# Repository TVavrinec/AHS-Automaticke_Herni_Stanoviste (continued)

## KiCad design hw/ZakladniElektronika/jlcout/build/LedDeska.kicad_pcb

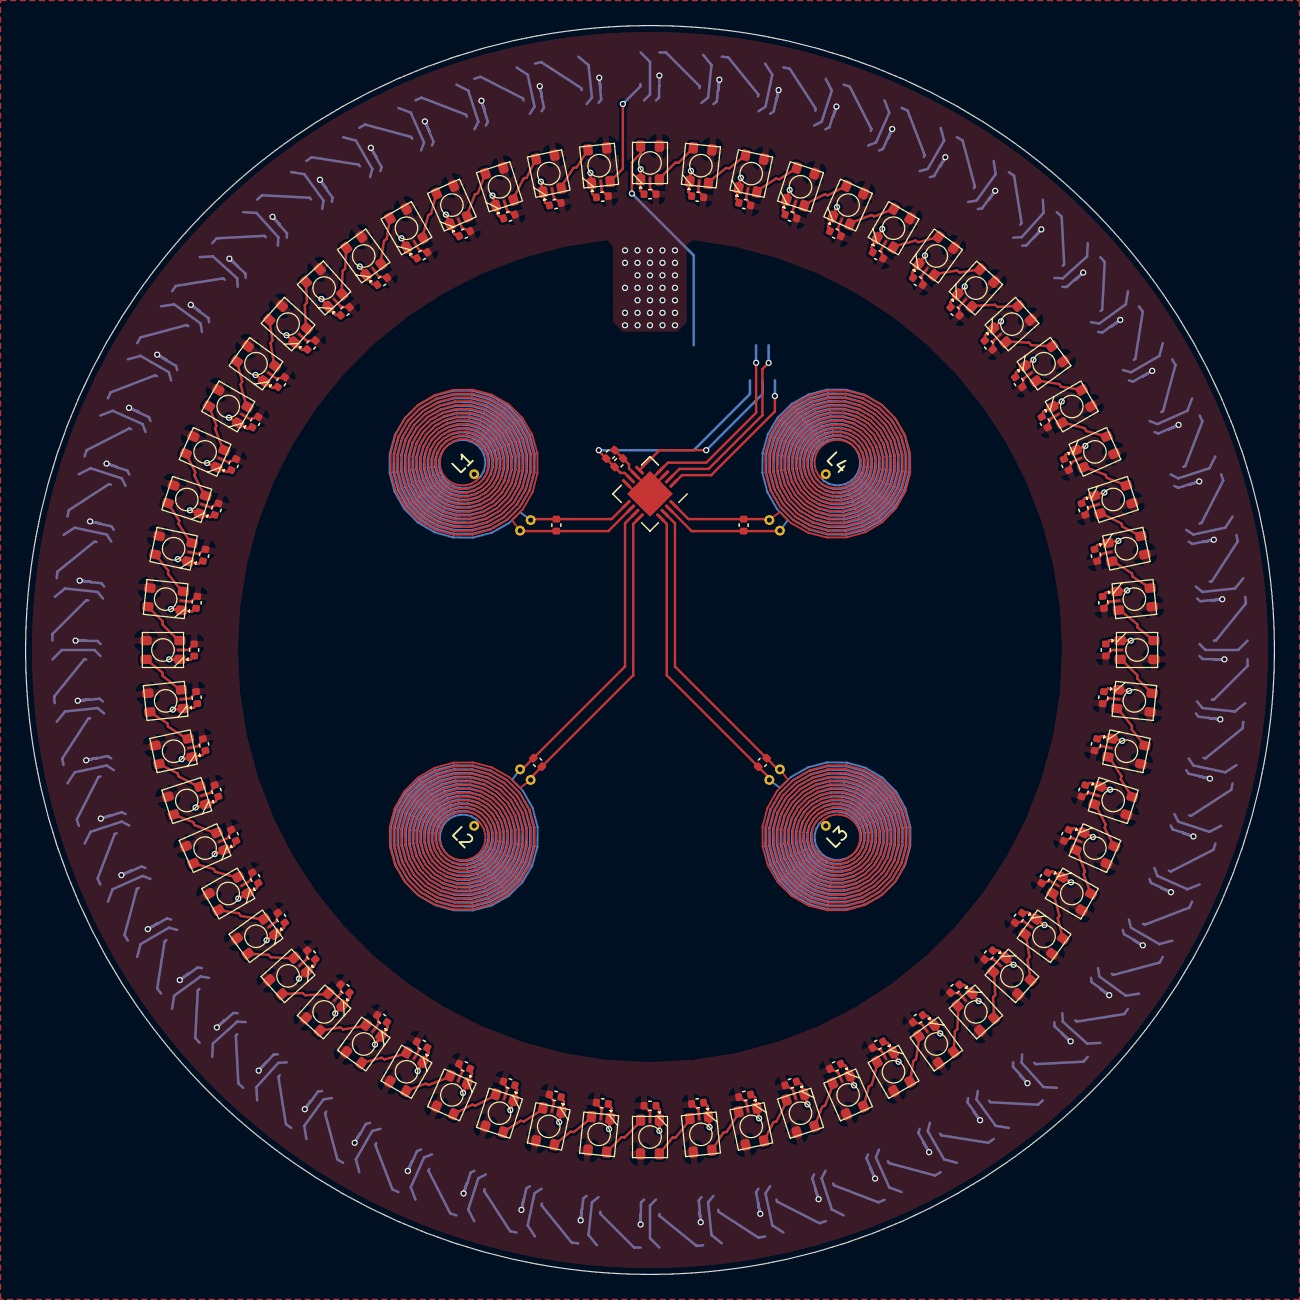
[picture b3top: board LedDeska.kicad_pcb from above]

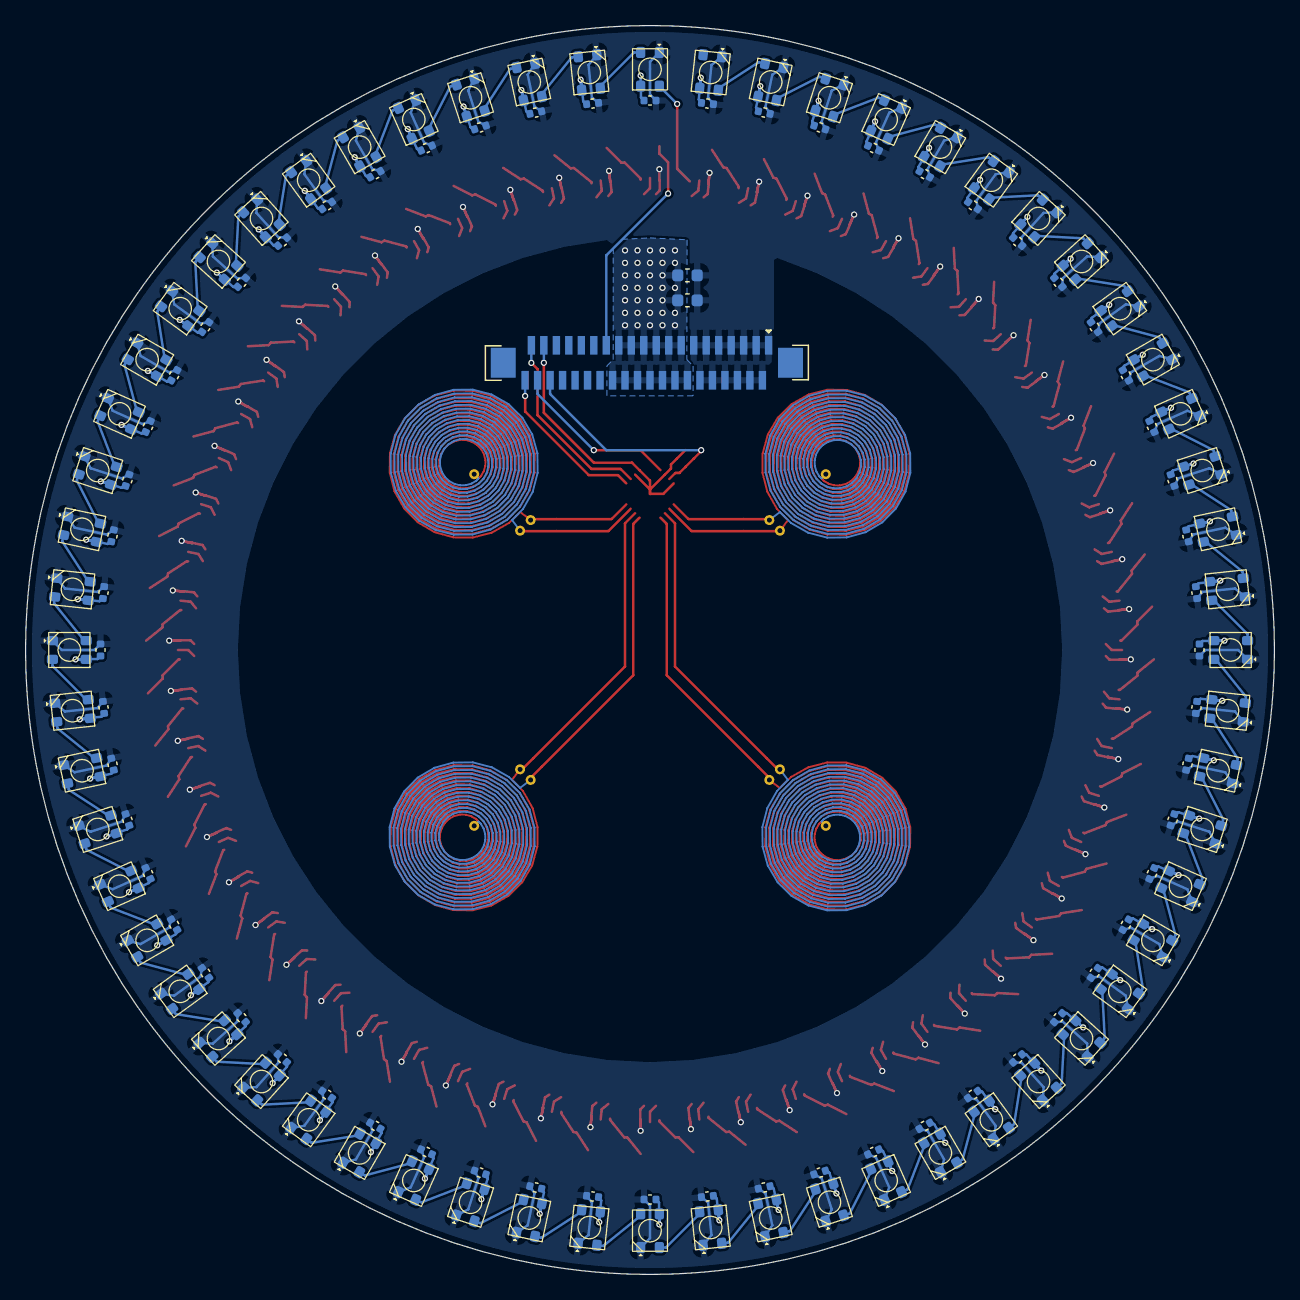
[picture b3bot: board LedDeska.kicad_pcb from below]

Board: 2 copper layers, 100.0 x 100.0 mm, 254 parts (123 on the bottom side), 135 nets.

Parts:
C1, C2: 10u; C_0603_1608Metric
C3: 1u; C_0402_1005Metric
C4, C12, C13, C14, C15, C16, C17, C18, C19, C20, C21, C22, C23, C24, C25, C26, C27, C28, C29, C30, C31, C32, C33, C34, C35, C36, C37, C38, C39, C40, C41, C42, C43, C44, C45, C46, C47, C48, C49, C50, C51, C52, C53, C54, C55, C56, C57, C58, C59, C60, C61, C62, C63, C64, C65, C66, C67, C68, C69, C70, C71, C72, C73, C74, C75, C76, C77, C78, C79, C80, C81, C82, C83, C84, C85, C86, C87, C88, C89, C90, C91, C92, C93, C94, C95, C96, C97, C98, C99, C100, C101, C102, C103, C104, C105, C106, C107, C108, C109, C110, C111, C112, C113, C114, C115, C116, C117, C118, C119, C120, C121, C122, C123, C124, C125, C126, C127, C128, C129, C130, C131: 100n; C_0402_1005Metric
C8, C9, C10, C11: 1000p; C_0402_1005Metric
D1, D2, D3, D4, D5, D6, D7, D8, D9, D10, D11, D12, D13, D14, D15, D16, D17, D18, D19, D20, D21, D22, D23, D24, D25, D26, D27, D28, D29, D30, D31, D32, D33, D34, D35, D36, D37, D38, D39, D40, D41, D42, D43, D44, D45, D46, D47, D48, D49, D50, D51, D52, D53, D54, D55, D56, D57, D58, D59, D60, D61, D62, D63, D64, D65, D66, D67, D68, D69, D70, D71, D72, D73, D74, D75, D76, D77, D78, D79, D80, D81, D82, D83, D84, D85, D86, D87, D88, D89, D90, D91, D92, D93, D94, D95, D96, D97, D98, D99, D100, D101, D102, D103, D104, D105, D106, D107, D108, D109, D110, D111, D112, D113, D114, D115, D116, D117, D118, D119, D120: WS2812B; 3528RGBW-WS2812B
J10: Conn_01x40; AFC11-S40ICC-00
L1, L2, L3, L4: 5.738 µH; PCB_coil
U1: LDC1614; WQFN-16-1EP_4x4mm_P0.5mm_EP2.6x2.6mm

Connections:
/LedDeska/3V3: C3.1, C4.1, J10.36, U1.7 (VDD)
/LedDeska/5V: C1.1, C2.1, C12.1, C13.1, C14.1, C15.1, C16.1, C17.1, C18.1, C19.1, C20.1, C21.1, C22.1, C23.1, C24.1, C25.1, C26.1, C27.1, C28.1, C29.1, C30.1, C31.1, C32.1, C33.1, C34.1, C35.1, C36.1, C37.1, C38.1, C39.1, C40.1, C41.1, C42.1, C43.1, C44.1, C45.1, C46.1, C47.1, C48.1, C49.1, C50.1, C51.1, C52.1, C53.1, C54.1, C55.1, C56.1, C57.1, C58.1, C59.1, C60.1, C61.1, C62.1, C63.1, C64.1, C65.1, C66.1, C67.1, C68.1, C69.1, C70.1, C71.1, C72.1, C73.1, C74.1, C75.1, C76.1, C77.1, C78.1, C79.1, C80.1, C81.1, C82.1, C83.1, C84.1, C85.1, C86.1, C87.1, C88.1, C89.1, C90.1, C91.1, C92.1, C93.1, C94.1, C95.1, C96.1, C97.1, C98.1, C99.1, C100.1, C101.1, C102.1, C103.1, C104.1, C105.1, C106.1, C107.1, C108.1, C109.1, C110.1, C111.1, C112.1, C113.1, C114.1, C115.1, C116.1, C117.1, C118.1, C119.1, C120.1, C121.1, C122.1, C123.1, C124.1, C125.1, C126.1, C127.1, C128.1, C129.1, C130.1, C131.1, D1.1 (VDD), D2.1 (VDD), D3.1 (VDD), D4.1 (VDD), D5.1 (VDD), D6.1 (VDD), D7.1 (VDD), D8.1 (VDD), D9.1 (VDD), D10.1 (VDD), D11.1 (VDD), D12.1 (VDD), D13.1 (VDD), D14.1 (VDD), D15.1 (VDD), D16.1 (VDD), D17.1 (VDD), D18.1 (VDD), D19.1 (VDD), D20.1 (VDD), D21.1 (VDD), D22.1 (VDD), D23.1 (VDD), D24.1 (VDD), D25.1 (VDD), D26.1 (VDD), D27.1 (VDD), D28.1 (VDD), D29.1 (VDD), D30.1 (VDD), D31.1 (VDD), D32.1 (VDD), D33.1 (VDD), D34.1 (VDD), D35.1 (VDD), D36.1 (VDD), D37.1 (VDD), D38.1 (VDD), D39.1 (VDD), D40.1 (VDD), D41.1 (VDD), D42.1 (VDD), D43.1 (VDD), D44.1 (VDD), D45.1 (VDD), D46.1 (VDD), D47.1 (VDD), D48.1 (VDD), D49.1 (VDD), D50.1 (VDD), D51.1 (VDD), D52.1 (VDD), D53.1 (VDD), D54.1 (VDD), D55.1 (VDD), D56.1 (VDD), D57.1 (VDD), D58.1 (VDD), D59.1 (VDD), D60.1 (VDD), D61.1 (VDD), D62.1 (VDD), D63.1 (VDD), D64.1 (VDD), D65.1 (VDD), D66.1 (VDD), D67.1 (VDD), D68.1 (VDD), D69.1 (VDD), D70.1 (VDD), D71.1 (VDD), D72.1 (VDD), D73.1 (VDD), D74.1 (VDD), D75.1 (VDD), D76.1 (VDD), D77.1 (VDD), D78.1 (VDD), D79.1 (VDD), D80.1 (VDD), D81.1 (VDD), D82.1 (VDD), D83.1 (VDD), D84.1 (VDD), D85.1 (VDD), D86.1 (VDD), D87.1 (VDD), D88.1 (VDD), D89.1 (VDD), D90.1 (VDD), D91.1 (VDD), D92.1 (VDD), D93.1 (VDD), D94.1 (VDD), D95.1 (VDD), D96.1 (VDD), D97.1 (VDD), D98.1 (VDD), D99.1 (VDD), D100.1 (VDD), D101.1 (VDD), D102.1 (VDD), D103.1 (VDD), D104.1 (VDD), D105.1 (VDD), D106.1 (VDD), D107.1 (VDD), D108.1 (VDD), D109.1 (VDD), D110.1 (VDD), D111.1 (VDD), D112.1 (VDD), D113.1 (VDD), D114.1 (VDD), D115.1 (VDD), D116.1 (VDD), D117.1 (VDD), D118.1 (VDD), D119.1 (VDD), D120.1 (VDD), J10.1, J10.2, J10.3, J10.4, J10.5, J10.6, J10.7, J10.8, J10.9, J10.10, J10.11, J10.12, J10.13
/LedDeska/AN-GND: C3.2, C4.2, J10.37, U1.3 (CLKIN), U1.4 (ADDR), U1.6 (SD), U1.8 (GND), U1.17 (GND)
/LedDeska/INT-LDC: J10.38, U1.5 (INTB)
/LedDeska/LED-GND: C1.2, C2.2, C12.2, C13.2, C14.2, C15.2, C16.2, C17.2, C18.2, C19.2, C20.2, C21.2, C22.2, C23.2, C24.2, C25.2, C26.2, C27.2, C28.2, C29.2, C30.2, C31.2, C32.2, C33.2, C34.2, C35.2, C36.2, C37.2, C38.2, C39.2, C40.2, C41.2, C42.2, C43.2, C44.2, C45.2, C46.2, C47.2, C48.2, C49.2, C50.2, C51.2, C52.2, C53.2, C54.2, C55.2, C56.2, C57.2, C58.2, C59.2, C60.2, C61.2, C62.2, C63.2, C64.2, C65.2, C66.2, C67.2, C68.2, C69.2, C70.2, C71.2, C72.2, C73.2, C74.2, C75.2, C76.2, C77.2, C78.2, C79.2, C80.2, C81.2, C82.2, C83.2, C84.2, C85.2, C86.2, C87.2, C88.2, C89.2, C90.2, C91.2, C92.2, C93.2, C94.2, C95.2, C96.2, C97.2, C98.2, C99.2, C100.2, C101.2, C102.2, C103.2, C104.2, C105.2, C106.2, C107.2, C108.2, C109.2, C110.2, C111.2, C112.2, C113.2, C114.2, C115.2, C116.2, C117.2, C118.2, C119.2, C120.2, C121.2, C122.2, C123.2, C124.2, C125.2, C126.2, C127.2, C128.2, C129.2, C130.2, C131.2, D1.3 (VSS), D2.3 (VSS), D3.3 (VSS), D4.3 (VSS), D5.3 (VSS), D6.3 (VSS), D7.3 (VSS), D8.3 (VSS), D9.3 (VSS), D10.3 (VSS), D11.3 (VSS), D12.3 (VSS), D13.3 (VSS), D14.3 (VSS), D15.3 (VSS), D16.3 (VSS), D17.3 (VSS), D18.3 (VSS), D19.3 (VSS), D20.3 (VSS), D21.3 (VSS), D22.3 (VSS), D23.3 (VSS), D24.3 (VSS), D25.3 (VSS), D26.3 (VSS), D27.3 (VSS), D28.3 (VSS), D29.3 (VSS), D30.3 (VSS), D31.3 (VSS), D32.3 (VSS), D33.3 (VSS), D34.3 (VSS), D35.3 (VSS), D36.3 (VSS), D37.3 (VSS), D38.3 (VSS), D39.3 (VSS), D40.3 (VSS), D41.3 (VSS), D42.3 (VSS), D43.3 (VSS), D44.3 (VSS), D45.3 (VSS), D46.3 (VSS), D47.3 (VSS), D48.3 (VSS), D49.3 (VSS), D50.3 (VSS), D51.3 (VSS), D52.3 (VSS), D53.3 (VSS), D54.3 (VSS), D55.3 (VSS), D56.3 (VSS), D57.3 (VSS), D58.3 (VSS), D59.3 (VSS), D60.3 (VSS), D61.3 (VSS), D62.3 (VSS), D63.3 (VSS), D64.3 (VSS), D65.3 (VSS), D66.3 (VSS), D67.3 (VSS), D68.3 (VSS), D69.3 (VSS), D70.3 (VSS), D71.3 (VSS), D72.3 (VSS), D73.3 (VSS), D74.3 (VSS), D75.3 (VSS), D76.3 (VSS), D77.3 (VSS), D78.3 (VSS), D79.3 (VSS), D80.3 (VSS), D81.3 (VSS), D82.3 (VSS), D83.3 (VSS), D84.3 (VSS), D85.3 (VSS), D86.3 (VSS), D87.3 (VSS), D88.3 (VSS), D89.3 (VSS), D90.3 (VSS), D91.3 (VSS), D92.3 (VSS), D93.3 (VSS), D94.3 (VSS), D95.3 (VSS), D96.3 (VSS), D97.3 (VSS), D98.3 (VSS), D99.3 (VSS), D100.3 (VSS), D101.3 (VSS), D102.3 (VSS), D103.3 (VSS), D104.3 (VSS), D105.3 (VSS), D106.3 (VSS), D107.3 (VSS), D108.3 (VSS), D109.3 (VSS), D110.3 (VSS), D111.3 (VSS), D112.3 (VSS), D113.3 (VSS), D114.3 (VSS), D115.3 (VSS), D116.3 (VSS), D117.3 (VSS), D118.3 (VSS), D119.3 (VSS), D120.3 (VSS), J10.14, J10.15, J10.16, J10.17, J10.18, J10.19, J10.20, J10.21, J10.22, J10.23, J10.24, J10.25, J10.26
/LedDeska/LedRing-Axial/DOUT: D60.2 (DOUT), D61.4 (DIN)
/LedDeska/SCL: J10.40, U1.1 (SCL)
/LedDeska/SDA: J10.39, U1.2 (SDA)
/LedDeska/WS2812: D1.4 (DIN), J10.27
unnamed: D1.2 (DOUT), D2.4 (DIN)
unnamed: D2.2 (DOUT), D3.4 (DIN)
unnamed: D3.2 (DOUT), D4.4 (DIN)
unnamed: D4.2 (DOUT), D5.4 (DIN)
unnamed: D5.2 (DOUT), D6.4 (DIN)
unnamed: D6.2 (DOUT), D7.4 (DIN)
unnamed: D7.2 (DOUT), D8.4 (DIN)
unnamed: D8.2 (DOUT), D9.4 (DIN)
unnamed: D9.2 (DOUT), D10.4 (DIN)
unnamed: D10.2 (DOUT), D11.4 (DIN)
unnamed: D11.2 (DOUT), D12.4 (DIN)
unnamed: D12.2 (DOUT), D13.4 (DIN)
unnamed: D13.2 (DOUT), D14.4 (DIN)
unnamed: D14.2 (DOUT), D15.4 (DIN)
unnamed: D15.2 (DOUT), D16.4 (DIN)
unnamed: D16.2 (DOUT), D17.4 (DIN)
unnamed: D17.2 (DOUT), D18.4 (DIN)
unnamed: D18.2 (DOUT), D19.4 (DIN)
unnamed: D19.2 (DOUT), D20.4 (DIN)
unnamed: D20.2 (DOUT), D21.4 (DIN)
unnamed: D21.2 (DOUT), D22.4 (DIN)
unnamed: D22.2 (DOUT), D23.4 (DIN)
unnamed: D23.2 (DOUT), D24.4 (DIN)
unnamed: D24.2 (DOUT), D25.4 (DIN)
unnamed: D25.2 (DOUT), D26.4 (DIN)
unnamed: D26.2 (DOUT), D27.4 (DIN)
unnamed: D27.2 (DOUT), D28.4 (DIN)
unnamed: D28.2 (DOUT), D29.4 (DIN)
unnamed: D29.2 (DOUT), D30.4 (DIN)
unnamed: D30.2 (DOUT), D31.4 (DIN)
unnamed: D31.2 (DOUT), D32.4 (DIN)
unnamed: D32.2 (DOUT), D33.4 (DIN)
unnamed: D33.2 (DOUT), D34.4 (DIN)
unnamed: D34.2 (DOUT), D35.4 (DIN)
unnamed: D35.2 (DOUT), D36.4 (DIN)
unnamed: D36.2 (DOUT), D37.4 (DIN)
unnamed: D37.2 (DOUT), D38.4 (DIN)
unnamed: D38.2 (DOUT), D39.4 (DIN)
unnamed: D39.2 (DOUT), D40.4 (DIN)
unnamed: D40.2 (DOUT), D41.4 (DIN)
unnamed: D41.2 (DOUT), D42.4 (DIN)
unnamed: D42.2 (DOUT), D43.4 (DIN)
unnamed: D43.2 (DOUT), D44.4 (DIN)
unnamed: D44.2 (DOUT), D45.4 (DIN)
unnamed: D45.2 (DOUT), D46.4 (DIN)
unnamed: D46.2 (DOUT), D47.4 (DIN)
unnamed: D47.2 (DOUT), D48.4 (DIN)
unnamed: D48.2 (DOUT), D49.4 (DIN)
unnamed: D49.2 (DOUT), D50.4 (DIN)
unnamed: D50.2 (DOUT), D51.4 (DIN)
unnamed: D51.2 (DOUT), D52.4 (DIN)
unnamed: D52.2 (DOUT), D53.4 (DIN)
unnamed: D53.2 (DOUT), D54.4 (DIN)
unnamed: D54.2 (DOUT), D55.4 (DIN)
unnamed: D55.2 (DOUT), D56.4 (DIN)
unnamed: D56.2 (DOUT), D57.4 (DIN)
unnamed: D57.2 (DOUT), D58.4 (DIN)
unnamed: D58.2 (DOUT), D59.4 (DIN)
unnamed: D59.2 (DOUT), D60.4 (DIN)
unnamed: D61.2 (DOUT), D62.4 (DIN)
unnamed: D62.2 (DOUT), D63.4 (DIN)
unnamed: D63.2 (DOUT), D64.4 (DIN)
unnamed: D64.2 (DOUT), D65.4 (DIN)
unnamed: D65.2 (DOUT), D66.4 (DIN)
unnamed: D66.2 (DOUT), D67.4 (DIN)
unnamed: D67.2 (DOUT), D68.4 (DIN)
unnamed: D68.2 (DOUT), D69.4 (DIN)
unnamed: D69.2 (DOUT), D70.4 (DIN)
unnamed: D70.2 (DOUT), D71.4 (DIN)
unnamed: D71.2 (DOUT), D72.4 (DIN)
unnamed: D72.2 (DOUT), D73.4 (DIN)
unnamed: D73.2 (DOUT), D74.4 (DIN)
unnamed: D74.2 (DOUT), D75.4 (DIN)
unnamed: D75.2 (DOUT), D76.4 (DIN)
unnamed: D76.2 (DOUT), D77.4 (DIN)
unnamed: D77.2 (DOUT), D78.4 (DIN)
unnamed: D78.2 (DOUT), D79.4 (DIN)
unnamed: D79.2 (DOUT), D80.4 (DIN)
unnamed: D80.2 (DOUT), D81.4 (DIN)
unnamed: D81.2 (DOUT), D82.4 (DIN)
unnamed: D82.2 (DOUT), D83.4 (DIN)
unnamed: D83.2 (DOUT), D84.4 (DIN)
unnamed: D84.2 (DOUT), D85.4 (DIN)
unnamed: D85.2 (DOUT), D86.4 (DIN)
unnamed: D86.2 (DOUT), D87.4 (DIN)
unnamed: D87.2 (DOUT), D88.4 (DIN)
unnamed: D88.2 (DOUT), D89.4 (DIN)
unnamed: D89.2 (DOUT), D90.4 (DIN)
unnamed: D90.2 (DOUT), D91.4 (DIN)
unnamed: D91.2 (DOUT), D92.4 (DIN)
unnamed: D92.2 (DOUT), D93.4 (DIN)
unnamed: D93.2 (DOUT), D94.4 (DIN)
unnamed: D94.2 (DOUT), D95.4 (DIN)
unnamed: D95.2 (DOUT), D96.4 (DIN)
unnamed: D96.2 (DOUT), D97.4 (DIN)
unnamed: D97.2 (DOUT), D98.4 (DIN)
unnamed: D98.2 (DOUT), D99.4 (DIN)
unnamed: D99.2 (DOUT), D100.4 (DIN)
unnamed: D100.2 (DOUT), D101.4 (DIN)
unnamed: D101.2 (DOUT), D102.4 (DIN)
unnamed: D102.2 (DOUT), D103.4 (DIN)
unnamed: D103.2 (DOUT), D104.4 (DIN)
unnamed: D104.2 (DOUT), D105.4 (DIN)
unnamed: D105.2 (DOUT), D106.4 (DIN)
unnamed: D106.2 (DOUT), D107.4 (DIN)
unnamed: D107.2 (DOUT), D108.4 (DIN)
unnamed: D108.2 (DOUT), D109.4 (DIN)
unnamed: D109.2 (DOUT), D110.4 (DIN)
unnamed: D110.2 (DOUT), D111.4 (DIN)
unnamed: D111.2 (DOUT), D112.4 (DIN)
unnamed: D112.2 (DOUT), D113.4 (DIN)
unnamed: D113.2 (DOUT), D114.4 (DIN)
unnamed: D114.2 (DOUT), D115.4 (DIN)
unnamed: D115.2 (DOUT), D116.4 (DIN)
unnamed: D116.2 (DOUT), D117.4 (DIN)
unnamed: D117.2 (DOUT), D118.4 (DIN)
unnamed: D118.2 (DOUT), D119.4 (DIN)
unnamed: D119.2 (DOUT), D120.4 (DIN)
unnamed: C8.1, L1.2, U1.9 (IN0A)
unnamed: C8.2, L1.1, U1.10 (IN0B)
unnamed: C9.1, L2.2, U1.11 (IN1A)
unnamed: C9.2, L2.1, U1.12 (IN1B)
unnamed: C10.1, L3.2, U1.13 (IN2A)
unnamed: C10.2, L3.1, U1.14 (IN2B)
unnamed: C11.1, L4.2, U1.15 (IN3A)
unnamed: C11.2, L4.1, U1.16 (IN3B)

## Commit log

2023-11-17 Nastin schematu
2023-12-03 Zaciame psat
2023-12-03 Trocha popisu
2023-12-06 Nějaká teorie her
2023-12-08 Zavazbení zapínání
2023-12-09 Rozšíření úvodu
2023-12-12 Přepys na case study
2023-12-16 Odevzdáno
2023-12-20 USB_multiplexer a přehlednost
2023-12-23 Likvidace MiniUI jako samostatné desky a výběr všech komponent
2023-12-26 Výmněna ochrany baterie
    Předchozí ochranný čip JLCPCB nemělo na skladě
2024-01-21 Hodnoty senzorických cívek
2024-01-21 gitignore
2024-03-08 AHS-V1
2024-05-24 Řešení issue "Držák baterek" a " SemiSemafor V0"
2024-05-24 Výrobní Makefiley
2024-05-24 .gitignore
2024-05-25 Řešení issue "Čtení zapínacího tlačítka"
2024-05-25 WPI (zápínací logika)
2025-03-21 KiCad V8
2025-03-21 Trocha textu
2025-04-04 Hw wip
2025-04-04 Text wip
2025-04-15 Hw PCB
2025-05-05 WPI text
2025-05-05 Bordel Hw
2025-06-11 Zacatek Prezentace
2025-07-09 konec
